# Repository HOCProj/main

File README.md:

**HOC Project**

*Hutchins-O'Dell-Cooper Senior Design Project Repository*

This project uses the following libraries and guides:

Adafruit MCP3008 library:
https://github.com/adafruit/Adafruit_Python_MCP3008

Twython AND Oauth:
https://www.raspberrypi.org/learning/getting-started-with-the-twitter-api/requirements/software/
https://www.raspberrypi.org/forums/viewtopic.php?t=162900&p=1054189

AVRDude:
http://www.raspihub.com/go/4c3370e8431b091c1698106135127581a646f3e2829fc26123d2bbfb34199dfa

SSMPT (Send email):
http://stackoverflow.com/questions/38391412/raspberry-pi-send-mail-from-command-line-using-gmail-smtp-server

Fetchmail (Receive email):
http://www.raspberry-projects.com/pi/software_utilities/email/fetchmail-to-receive-email

These libraries will be automatically downloaded and installed by executing the GitAll.py file. After installation, some parts require additional setup. Refer to the corresponding guide.

**User Manual**

Setup guides and example scripts are available in the appropriate folders (Raspberry Pi and ATTiny85).

The primary purpose of our project is to provide a cheap means of extending the capabilities of the Raspberry Pi and the ATTiny85. We also have the secondary purpose of compiling all of the necessary software and troubleshooting into one location, so that a person with beginner-intermediate level experience with circuitry and code can avoid the wiring mess of traditional electronics and the days or weeks of research into software.

On the board is a 40-pin header. This is used to connect our project to the Raspberry Pi. Doing so gives the Pi access to an MCP3008 ADC and an external power supply. There is also an 8-pin socket for an ATTiny85, which can be connected and interfaced with the IR receiver and the external power supply and ADC as well. The Raspberry Pi and ATTiny85 can be used simultaneously or separately. If using both of them and the ADC for either (cannot be used by both at one time), you must be mindful of shared connections. Refer to the board schematics.

A green screw block connector is situated next to the IR receiver. This can be used to receive external power (up to 33V and 3A continuous), and regulate it to ~5V for the Pi and ATTiny. Next to that is an 8-pin straight header. These are the analog inputs for the ADC, corresponding to channels 0-7. Next to that is a 2x4-pin header, which is laid out exactly the same as the ATTiny85 pins and is used to access those pins. Below that is a button which resets the ATTiny85 (pulls the RESET pin to ground).

There are two 2-pin headers, each labeled RPi and MCP. These are used to connect and disconnect power to the Raspberry Pi and MCP3008 respectively. If, for example, you want the ATTiny and Raspberry Pi to communicate over the ISP lines, the MCP header should be disconnected to prevent that chip from interfering with the signals. Or if you want the ATTiny to use the ADC and the Pi is not in use or powered separately, the RPi header should be disconnected.]

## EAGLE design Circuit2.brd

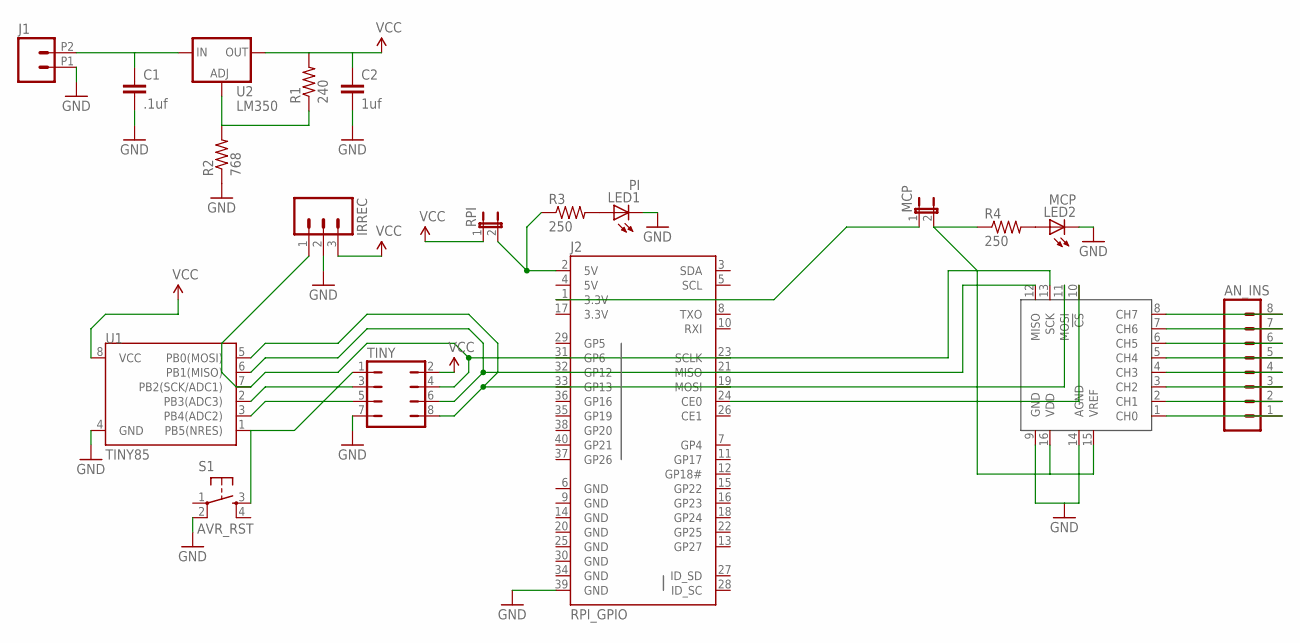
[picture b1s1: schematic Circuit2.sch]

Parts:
ADC: MCP3008SL; SO16
AN_INS: M08; 1X08_ROUND
C1: .1uf; 0805
C2: 1uf; 0805
IRREC: M03PTH; 1X03
J1: M022.54MM_SCREWTERM; 1X02_2.54_SCREWTERM
J2: RPI_GPIO; 2X20-SHROUDED
LED1: PI; LED-1206
LED2: MCP; LED-1206
MCP: JP1E; JP1
R1: 240; 0805
R2: 768; 0805
R3, R4: 250; 1206
RPI: JP1E; JP1
S1: AVR_RST; TAC-SWITCH-PTH
TINY: JP4Q
U1: TINY85; DIP08
U2: LM350; TO220-ADJ

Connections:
3.3V: J2.17 (3.3V)
5V: J2.4 (5V)
GND: ADC.9 (GND), ADC.14 (AGND), C1.2, C2.2, IRREC.2, J1.P1 (1), J2.6 (GND), J2.9 (GND), J2.14 (GND), J2.20 (GND), J2.25 (GND), J2.30 (GND), J2.34 (GND), J2.39 (GND), LED1.C, LED2.C, R2.1, S1.2, TINY.7, U1.4 (GND)
unnamed: ADC.11 (MOSI), J2.19 (MOSI), TINY.8, U1.5 (PB0(MOSI))
unnamed: ADC.12 (MISO), J2.21 (MISO), TINY.6, U1.6 (PB1(MISO))
unnamed: ADC.13 (SCK), IRREC.1, J2.23 (SCLK), TINY.4, U1.7 (PB2(SCK/ADC1))
unnamed: J2.2 (5V), R3.1, RPI.2
unnamed: TINY.3, U1.2 (PB3(ADC3))
unnamed: S1.3, TINY.1, U1.1 (PB5(NRES))
unnamed: TINY.5, U1.3 (PB4(ADC2))
unnamed: ADC.15 (VREF), ADC.16 (VDD), MCP.2, R4.1
unnamed: R1.1, R2.2, U2.ADJ
unnamed: ADC.8 (CH7), AN_INS.8
unnamed: C1.1, J1.P2 (2), U2.IN
unnamed: ADC.10 (!CS), J2.24 (CE0)
unnamed: J2.1 (3.3V), MCP.1
unnamed: ADC.7 (CH6), AN_INS.7
unnamed: ADC.6 (CH5), AN_INS.6
unnamed: ADC.5 (CH4), AN_INS.5
unnamed: ADC.4 (CH3), AN_INS.4
unnamed: ADC.3 (CH2), AN_INS.3
unnamed: ADC.2 (CH1), AN_INS.2
unnamed: ADC.1 (CH0), AN_INS.1
unnamed: LED1.A, R3.2
unnamed: LED2.A, R4.2
VCC: C2.1, IRREC.3, R1.2, RPI.1, TINY.2, U1.8 (VCC), U2.OUT

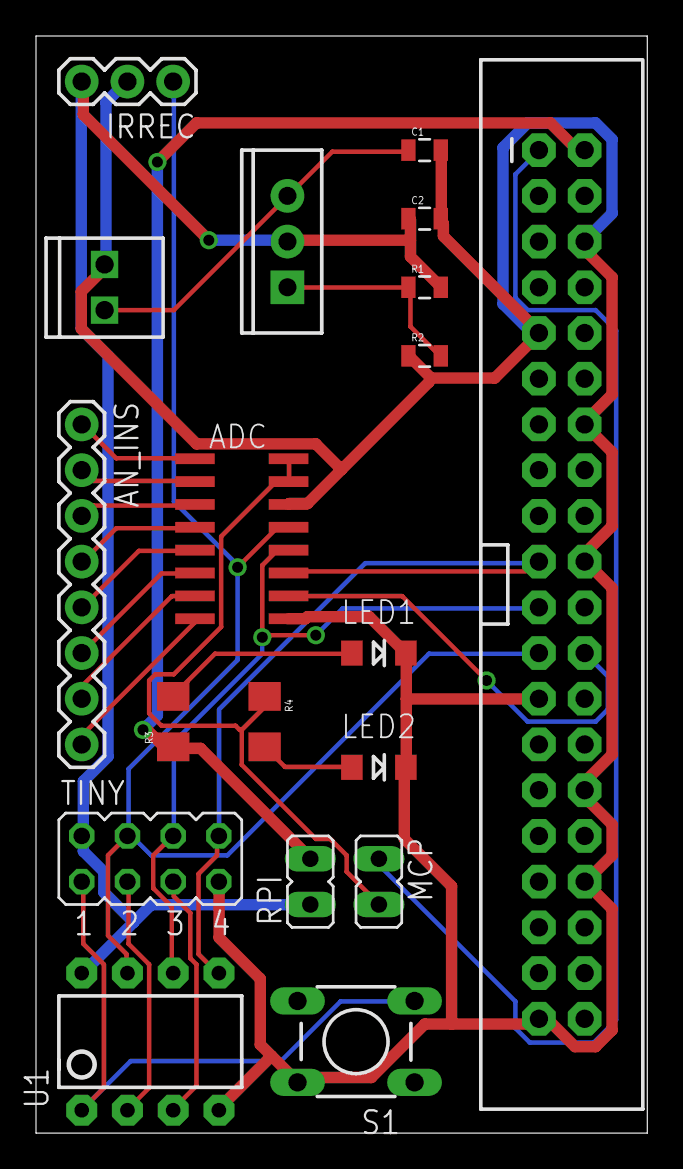
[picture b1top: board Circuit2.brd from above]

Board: 2 copper layers, 34.0 x 61.0 mm, 19 parts (0 on the bottom side), 24 nets.

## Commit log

2017-04-13 Create asdf
2017-04-26 Create sendmail
2017-04-26 Create sendtextfile
2017-04-28 Create getsubject
2017-05-01 Update DoSomethingIfTelegram
2017-05-03 Create emailip

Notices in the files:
parts and their libraries:
SparkFun-Connectors: Licensing: Creative Commons ShareAlike 4.0 International - https://creativecommons.org/licenses/by-sa/4.0
